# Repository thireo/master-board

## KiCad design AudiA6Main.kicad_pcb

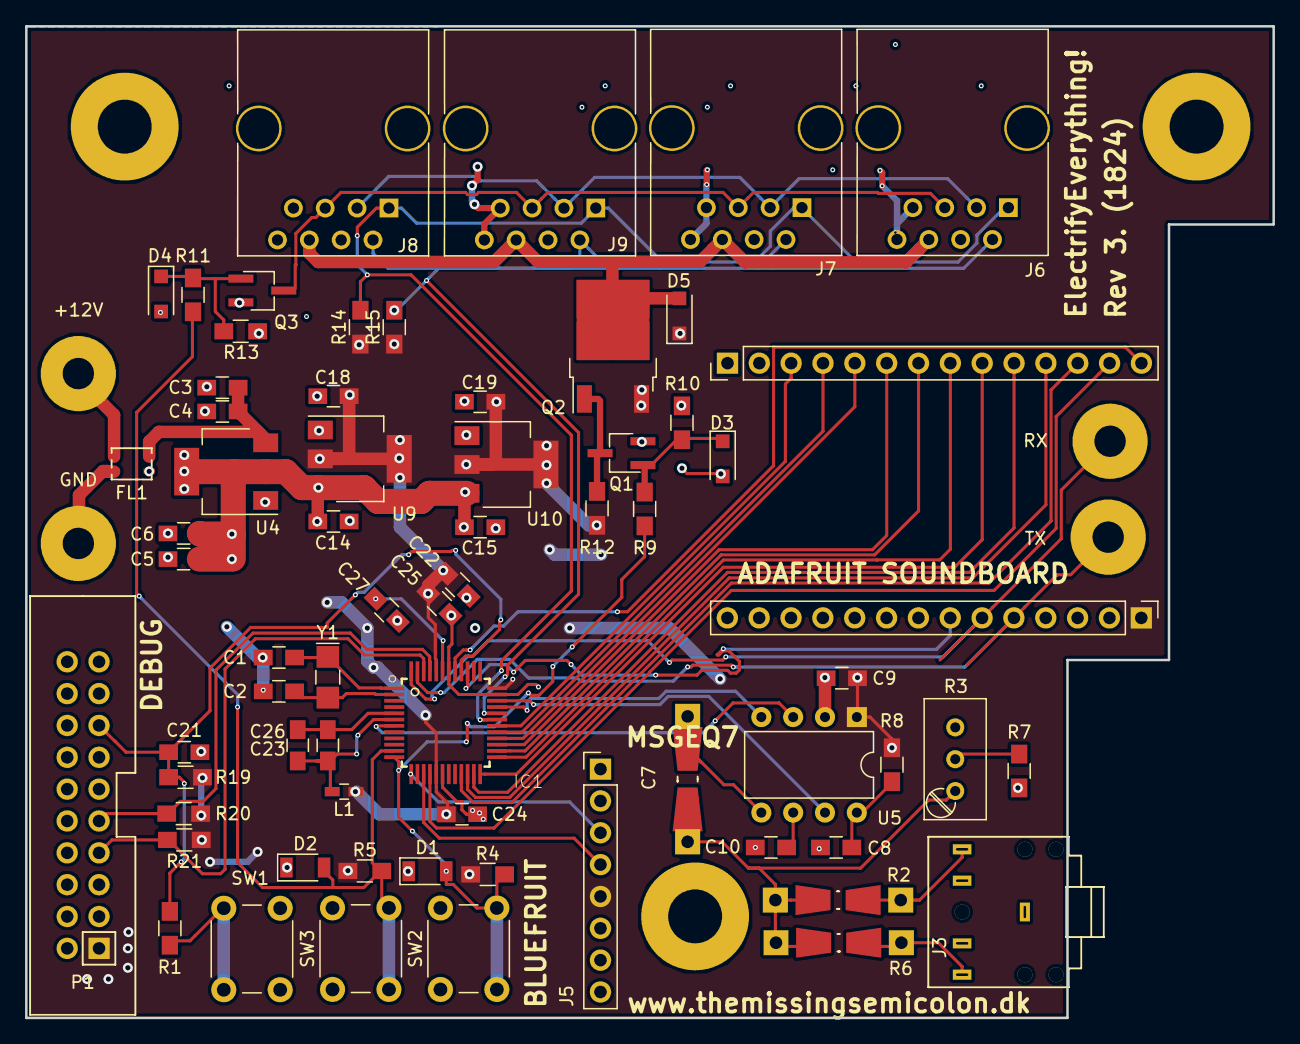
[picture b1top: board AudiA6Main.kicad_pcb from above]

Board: 2 copper layers, 99.5 x 79.1 mm, 71 parts (0 on the bottom side), 52 nets.

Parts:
+12V: 12V; SolderWirePad_single_2-5mmDrill
C1, C2: 15pF; C_0805_HandSoldering
C3, C4, C14, C15, C21, C24, C25, C26: 100nF; C_0805_HandSoldering
C5, C6, C18, C19, C22, C23: 10uF; C_0805_HandSoldering
C7: 68nF; Resistor_SMD+THTuniversal_0805to1206_RM10_HandSoldering
C8: 33pF; C_0805_HandSoldering
C9, C10: 0.1uF; C_0805_HandSoldering
C27: 1uF; C_0805_HandSoldering
D1, D2: I2C PWR; D_1206
D3, D4, D5: D_Schottky; D_SOD-123F
FL1: ACP3225
GND: GND; SolderWirePad_single_2-5mmDrill
IC1: ATSAMD21G18A-AU; QFP50P900X900X120-48N
J3: Audio-Jack-4; SJ1-35235
J5: BLUEFRUIT; Pin_Header_Straight_1x08_Pitch2.54mm
J6, J7, J8, J9: RJ45; RJ45_8
J11, J12: Conn_01x14; Pin_Header_Straight_1x14_Pitch2.54mm
L1: Ferrite_Bead_Small; C_0603_HandSoldering
P1: CONN_02X10; SAM-ICE-Header
Q1, Q3: NTR5103NT1G; TSOT-23_HandSoldering
Q2: TP0610T; TO-252-2
R1: 330; R_0805_HandSoldering
R2, R6: 15k; Resistor_SMD+THTuniversal_0805to1206_RM10_HandSoldering_Rev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
R3: POT; Potentiometer_Trimmer_Bourns_3296W
R4, R5, R10, R12, R13, R14, R15: 10k; R_0805_HandSoldering
R7: 220; R_0805_HandSoldering
R8: 200k; R_0805_HandSoldering
R9, R11: 200; R_0805_HandSoldering
R19, R20, R21: 100kohm; R_0805_HandSoldering
RX: UART_RX; SolderWirePad_single_2-5mmDrill
SW1: SW_RESET; SW_PUSH_6mm
SW2: I2C_PWR; SW_PUSH_6mm
SW3: I2C_RESET; SW_PUSH_6mm
TX: UART_TX; SolderWirePad_single_2-5mmDrill
U4: LD1117S50TR_SOT223; SOT-223-3_TabPin2
U5: MSGEQ7; DIP-8_W7.62mm
U9, U10: AP1117-15; SOT-223-3_TabPin2
Y1: Crystal_Small; Crystal_SMD_G8-2pin_3.2x1.5mm_HandSoldering

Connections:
+5V: C5.1, C6.1, C14.1, C15.1, U4.2, U9.3, U10.3
+12V: C3.1, C4.1, FL1.4, U4.3
/BLE_RX: IC1.15, J5.4
/BLE_TX: IC1.13, J5.3
/CS: J6.3, J7.3, J8.3, J9.3
/DC_OUT: IC1.7, U5.3
/GNDANA: C23.2, C26.2, IC1.5
/I2C_PWR_EN: D1.2, IC1.12, R4.2, R9.2, SW2.2
/I2C_RESET: D2.2, IC1.11, R5.2, R11.2, SW3.2
/MCU_RESET: C21.1, IC1.40, P1.15, R1.1, R19.2
/SAMPLE_RESET: IC1.34, U5.7
/SAMPLE_STROBE: IC1.33, U5.4
/SB_BTN00: IC1.16, J11.13
/SB_BTN01: IC1.21, J11.12
/SB_BTN02: IC1.22, J11.11
/SB_BTN03: IC1.23, J11.10
/SB_BTN04: IC1.24, J11.9
/SB_BTN05: IC1.25, J11.8
/SB_BTN06: IC1.26, J11.7
/SB_BTN07: IC1.27, J11.6
/SB_BTN08: IC1.28, J11.5
/SB_BTN09: IC1.29, J11.4
/SB_BTN10: IC1.30, J11.3
/SB_RESET: IC1.41, J11.14
/SB_RX: IC1.48, J12.6, RX.1
/SB_TX: IC1.47, J12.5, TX.1
/SB_UG: IC1.39, J12.7
/SCL: IC1.32, J6.2, J7.2, J8.2, J9.2, R15.2
/SDA: IC1.31, J6.1, J7.1, J8.1, J9.1, R14.2
/SWCLK: IC1.45, P1.9, R20.2
/SWDIO: IC1.46, P1.7, R21.2
/VCC_I2C: D5.2, J6.6, J7.6, J8.6, J9.6, Q2.2
/VDDANA: C23.1, C26.1, IC1.6, L1.1
/VDDCORE: C27.1, IC1.43
/~RESET: J6.5, J7.5, J8.5, J9.5, Q3.3
GND: C1.2, C2.2, C3.2, C4.2, C5.2, C6.2, C8.1, C9.1, C10.2, C14.2, C15.2, C18.2, C19.2, C21.2, C22.2, C24.2, C25.2, C27.2, D1.1, D2.1, D3.2, D4.2, FL1.3, IC1.18, IC1.35, IC1.42, J3.1, J3.4, J5.2, J5.7, J6.7, J6.8, J7.7, J7.8, J8.7, J8.8, J9.7, J9.8, J11.1, J12.2, J12.11, J12.14, P1.4, P1.6, P1.8, P1.10, P1.12, P1.14, P1.16, P1.18, P1.20, Q1.2, Q3.2, R7.1, R10.2, R13.2, SW1.1, SW2.1, SW3.1, U4.1, U5.2, U9.1, U10.1
unnamed: C1.1, IC1.1, Y1.1
unnamed: C2.1, IC1.2, Y1.2
unnamed: C7.1, R2.1, R3.1, R6.1
unnamed: C7.2, U5.5
unnamed: C8.2, R8.1, U5.8
unnamed: C10.1, U5.6
unnamed: D3.1, Q1.1, R9.1, R10.1
unnamed: D4.1, Q3.1, R11.1, R13.1
unnamed: +12V.1, FL1.1
unnamed: FL1.2, GND.1
unnamed: J3.2, R2.2
unnamed: J3.3, R6.2
unnamed: Q1.3, Q2.1, R12.2
unnamed: R1.2, SW1.2
unnamed: R3.2, R7.2
VCC: C9.2, C18.1, C19.1, C22.1, C24.1, C25.1, D5.1, IC1.17, IC1.36, IC1.44, J5.5, J12.1, L1.2, P1.1, Q2.3, R4.1, R5.1, R8.2, R12.1, R14.1, R15.1, R19.1, R20.1, R21.1, U5.1, U9.2, U10.2

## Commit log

2020-08-21 Sorry future me
